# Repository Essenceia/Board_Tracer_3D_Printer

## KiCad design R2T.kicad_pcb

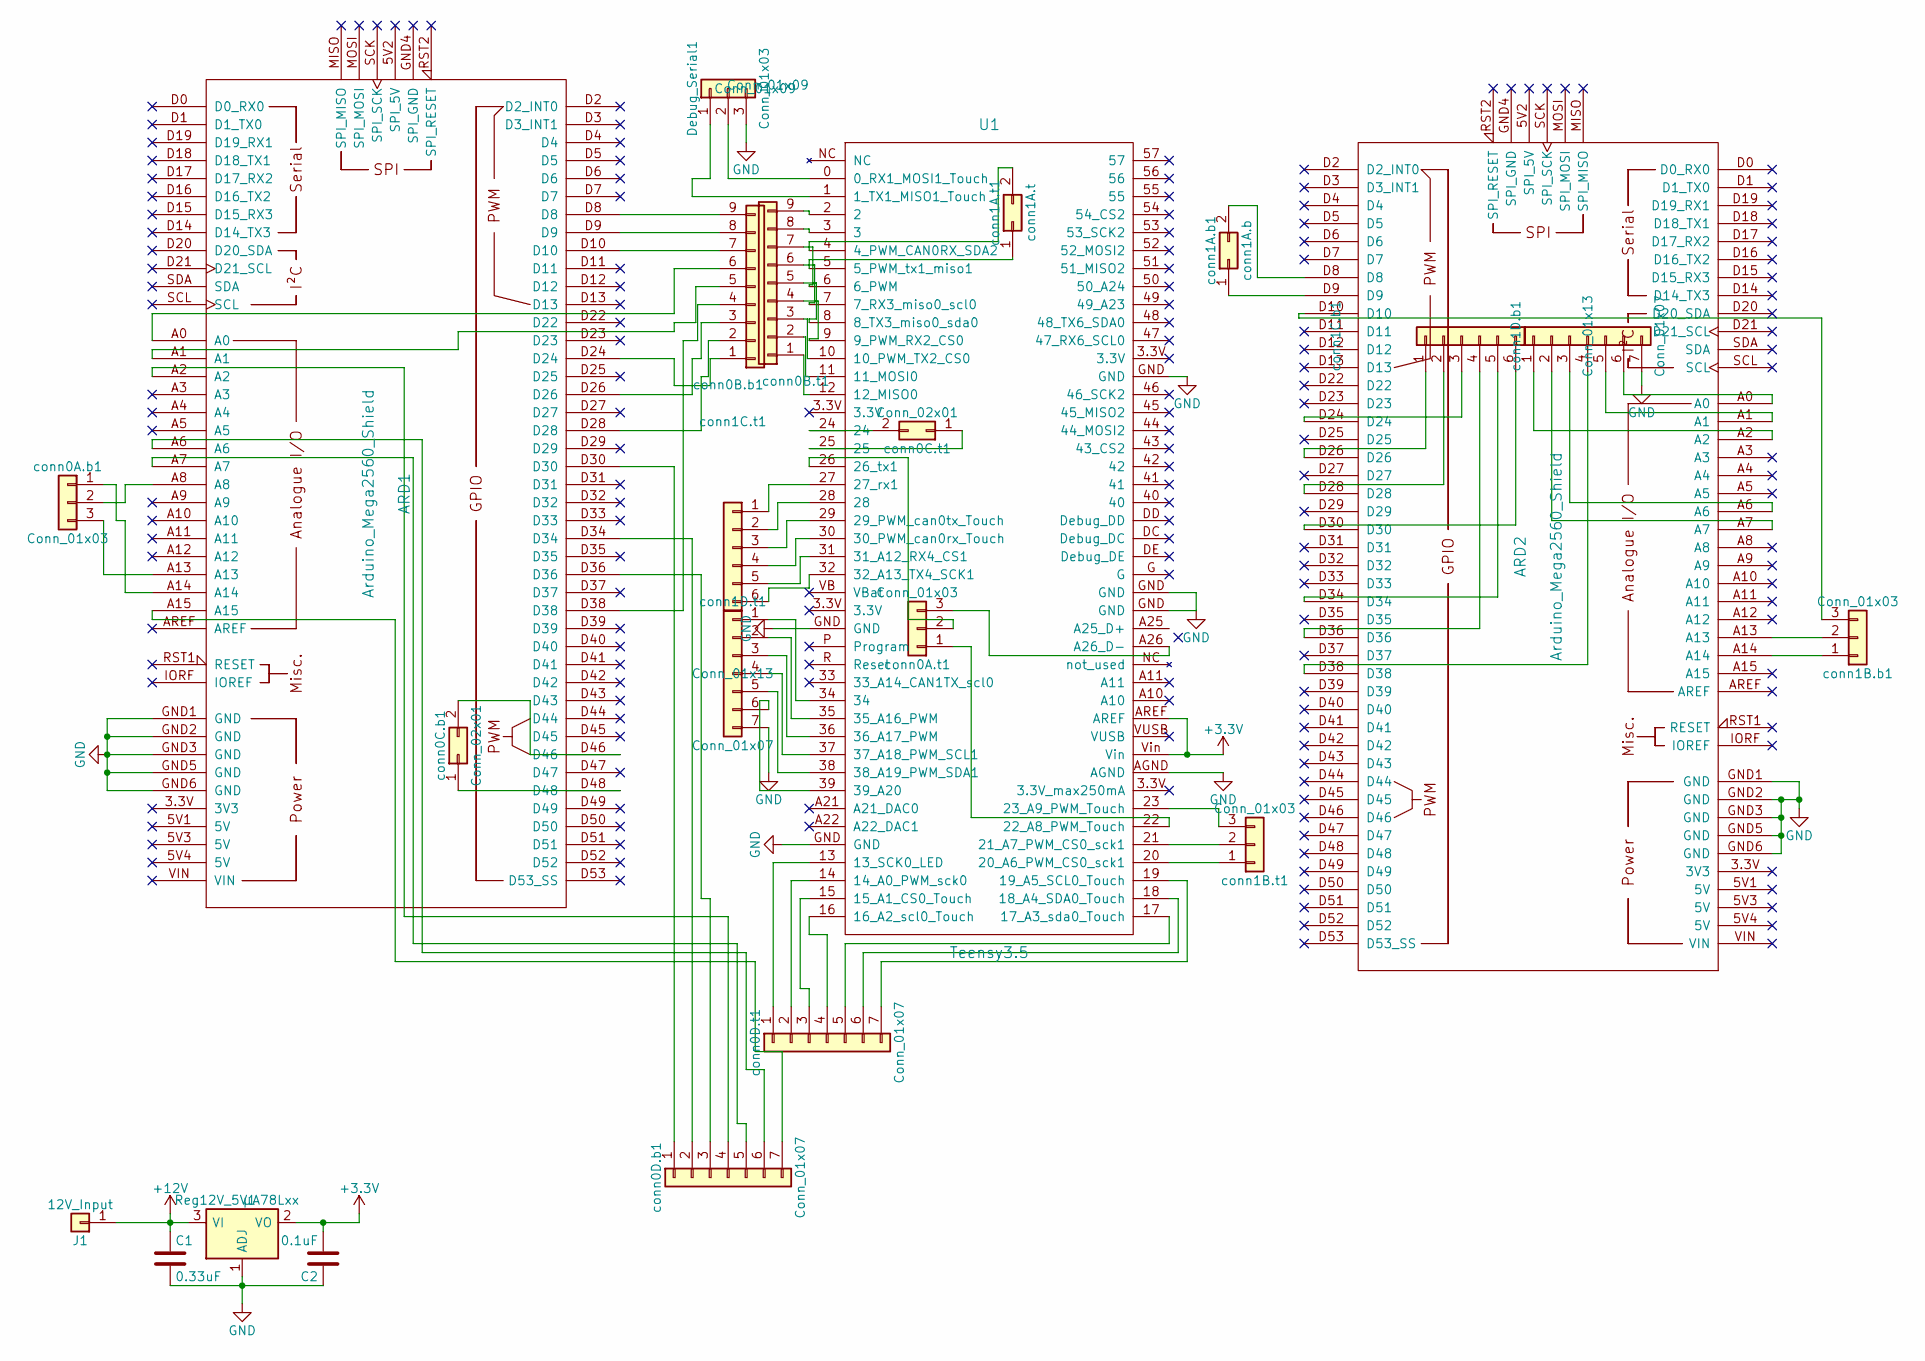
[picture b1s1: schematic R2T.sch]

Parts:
ARD1, ARD2: Arduino_Mega2560_Shield
C1: 0.33uF; PinSocket_1x02_P2.00mm_Vertical
C2: 0.1uF; PinSocket_1x02_P2.00mm_Vertical
Debug_Serial1: Conn_01x03; PinHeader_1x03_P2.00mm_Vertical
J1: 12V_Input; MountingHole_2.5mm_Pad
Reg12V_5V1: μA78Lxx; SOT-223-3_TabPin2
U1: Teensy3.5; Teensy35_36
conn0A.b1, conn0A.t1: Conn_01x03; PinHeader_1x03_P2.00mm_Vertical
conn0B.b1, conn0B.t1: Conn_01x09; PinHeader_1x09_P2.00mm_Vertical
conn0C.b1: Conn_02x01; PinSocket_2x01_P2.00mm_Vertical
conn0C.t1: Conn_02x01; PinSocket_1x02_P2.00mm_Horizontal
conn0D.b1, conn0D.t1, conn1D.b1, conn1D.t1: Conn_01x07; PinHeader_1x07_P2.00mm_Vertical
conn1A.b1: conn1A.b; PinSocket_2x01_P2.00mm_Vertical
conn1A.t1: conn1A.t; PinSocket_2x01_P2.00mm_Vertical
conn1B.b1, conn1B.t1: Conn_01x03; PinSocket_1x03_P2.00mm_Vertical
conn1C.b1, conn1C.t1: Conn_01x13; PinSocket_1x06_P2.00mm_Vertical

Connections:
+3V3: C2.2, Reg12V_5V1.2 (VO), U1.AREF, U1.Vin
+12V: C1.1, J1.1, Reg12V_5V1.3 (VI)
GND: ARD1.GND1 (GND), ARD1.GND2 (GND), ARD1.GND3 (GND), ARD1.GND5 (GND), ARD1.GND6 (GND), ARD2.GND1 (GND), ARD2.GND2 (GND), ARD2.GND3 (GND), ARD2.GND5 (GND), ARD2.GND6 (GND), C1.2, C2.1, Debug_Serial1.3, Reg12V_5V1.1 (ADJ), U1.AGND, U1.GND, conn1D.b1.7, conn1D.t1.7
unnamed: ARD1.A0, conn0B.b1.6
unnamed: ARD1.A1, conn0B.b1.5
unnamed: ARD1.A2, conn0D.b1.4
unnamed: ARD1.A6, conn0D.b1.6
unnamed: ARD1.A7, conn0D.b1.5
unnamed: ARD1.A8, conn0A.b1.2
unnamed: ARD1.A13, conn0A.b1.3
unnamed: ARD1.A14, conn0A.b1.1
unnamed: ARD1.A15, conn0D.b1.7
unnamed: ARD1.D8, conn0B.b1.9
unnamed: ARD1.D9, conn0B.b1.8
unnamed: ARD1.D10, conn0B.b1.7
unnamed: ARD1.D24, conn0B.b1.1
unnamed: ARD1.D26, conn0B.b1.3
unnamed: ARD1.D28, conn0B.b1.2
unnamed: ARD1.D30, conn0D.b1.1
unnamed: ARD1.D34, conn0D.b1.2
unnamed: ARD1.D36, conn0D.b1.3
unnamed: ARD1.D38, conn0B.b1.4
unnamed: ARD1.D46, conn0C.b1.2
unnamed: ARD1.D48, conn0C.b1.1
unnamed: ARD2.A0, conn1D.b1.6
unnamed: ARD2.A1, conn1D.b1.5
unnamed: ARD2.A2, conn1D.b1.1
unnamed: ARD2.A6, conn1D.b1.3
unnamed: ARD2.A7, conn1D.b1.2
unnamed: ARD2.A13, conn1B.b1.2
unnamed: ARD2.A14, conn1B.b1.1
unnamed: ARD2.D8, conn1A.b1.2
unnamed: ARD2.D9, conn1A.b1.1
unnamed: ARD2.D10, conn1B.b1.3
unnamed: ARD2.D24, conn1C.b1.3
unnamed: ARD2.D26, conn1C.b1.1
unnamed: ARD2.D28, conn1C.b1.2
unnamed: ARD2.D30, conn1C.b1.6
unnamed: ARD2.D34, conn1C.b1.5
unnamed: ARD2.D36, conn1C.b1.4
unnamed: ARD2.D38, conn1D.b1.4
unnamed: Debug_Serial1.1, U1.1 (1_TX1_MISO1_Touch)
unnamed: Debug_Serial1.2, U1.0 (0_RX1_MOSI1_Touch)
unnamed: U1.2, conn0B.t1.9
unnamed: U1.3, conn0B.t1.8
unnamed: U1.4 (4_PWM_CAN0RX_SDA2), conn1A.t1.2
unnamed: U1.5 (5_PWM_tx1_miso1), conn1A.t1.1
unnamed: U1.6 (6_PWM), conn0B.t1.7
unnamed: U1.7 (7_RX3_miso0_scl0), conn0B.t1.6
unnamed: U1.8 (8_TX3_miso0_sda0), conn0B.t1.5
unnamed: U1.9 (9_PWM_RX2_CS0), conn0B.t1.4
unnamed: U1.10 (10_PWM_TX2_CS0), conn0B.t1.3
unnamed: U1.11 (11_MOSI0), conn0B.t1.2
unnamed: U1.12 (12_MISO0), conn0B.t1.1
unnamed: U1.13 (13_SCK0_LED), conn0D.t1.1
unnamed: U1.14 (14_A0_PWM_sck0), conn0D.t1.2
unnamed: U1.15 (15_A1_CS0_Touch), conn0D.t1.3
unnamed: U1.16 (16_A2_scl0_Touch), conn0D.t1.4
unnamed: U1.17 (17_A3_sda0_Touch), conn0D.t1.5
unnamed: U1.18 (18_A4_SDA0_Touch), conn0D.t1.6
unnamed: U1.19 (19_A5_SCL0_Touch), conn0D.t1.7
unnamed: U1.20 (20_A6_PWM_CS0_sck1), conn1B.t1.1
unnamed: U1.21 (21_A7_PWM_CS0_sck1), conn1B.t1.2
unnamed: U1.22 (22_A8_PWM_Touch), conn0A.t1.1
unnamed: U1.23 (23_A9_PWM_Touch), conn1B.t1.3
unnamed: U1.24, conn0C.t1.2
unnamed: U1.25, conn0C.t1.1
unnamed: U1.26 (26_tx1), conn0A.t1.2
unnamed: U1.27 (27_rx1), conn1C.t1.1
unnamed: U1.28, conn1C.t1.2
unnamed: U1.29 (29_PWM_can0tx_Touch), conn1C.t1.3
unnamed: U1.30 (30_PWM_can0rx_Touch), conn1C.t1.4
unnamed: U1.31 (31_A12_RX4_CS1), conn1C.t1.5
unnamed: U1.32 (32_A13_TX4_SCK1), conn1C.t1.6
unnamed: U1.34, conn1D.t1.1
unnamed: U1.35 (35_A16_PWM), conn1D.t1.2
unnamed: U1.36 (36_A17_PWM), conn1D.t1.3
unnamed: U1.37 (37_A18_PWM_SCL1), conn1D.t1.4
unnamed: U1.38 (38_A19_PWM_SDA1), conn1D.t1.5
unnamed: U1.39 (39_A20), conn1D.t1.6
unnamed: U1.A26 (A26_D-), conn0A.t1.3

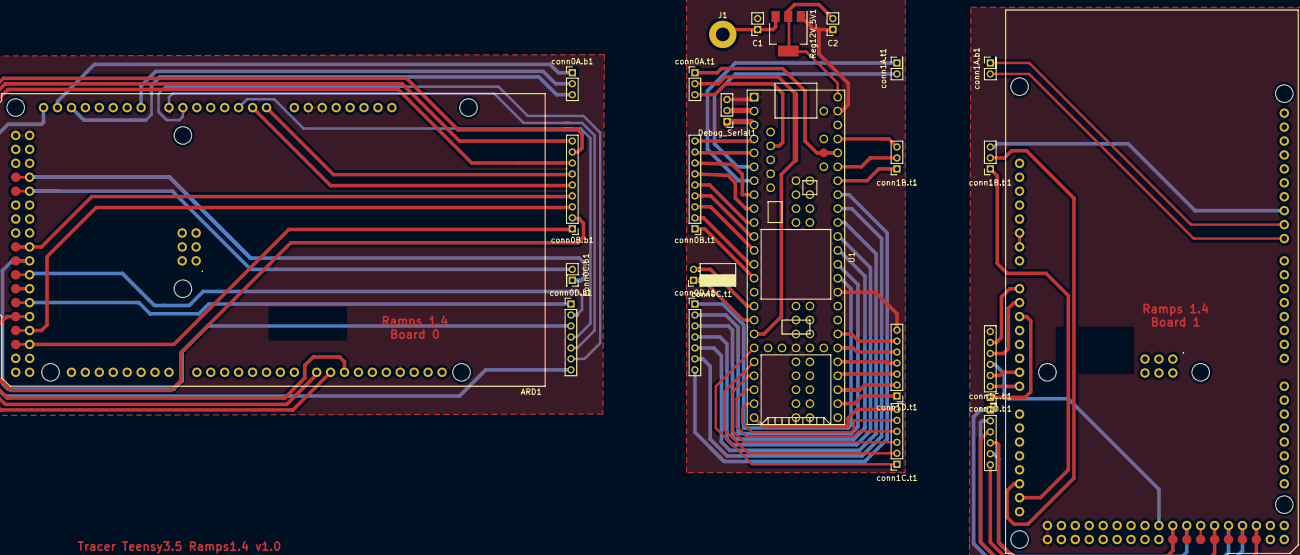
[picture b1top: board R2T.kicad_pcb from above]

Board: 2 copper layers, 24 parts (0 on the bottom side), 81 nets.

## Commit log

2018-01-10 Generated PDF files + finished routing. No vias in routing and shared GND. Expecting regulator 12 V to 5 V with package SOT 223 to power the teensy using the ramps power source
2018-01-10 Added connectors still need to switch serial from x02 pin to x03 pin add ground + biger wires for cnc engraving
2018-01-12 Added a 3rd pin on the connector for the serial debug on the teensy : gnd added
2018-01-13 Finished seperating circuits on to 3 diffrent boards : teensy / ramps 0 / ramps 1. Sill need to clean and optimis for space and soder
2018-01-13 Finished cleaning
